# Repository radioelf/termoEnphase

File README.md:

# termoEnphase
Control de termo eléctrico según excedentes de sistema fotovoltaico con Enphase

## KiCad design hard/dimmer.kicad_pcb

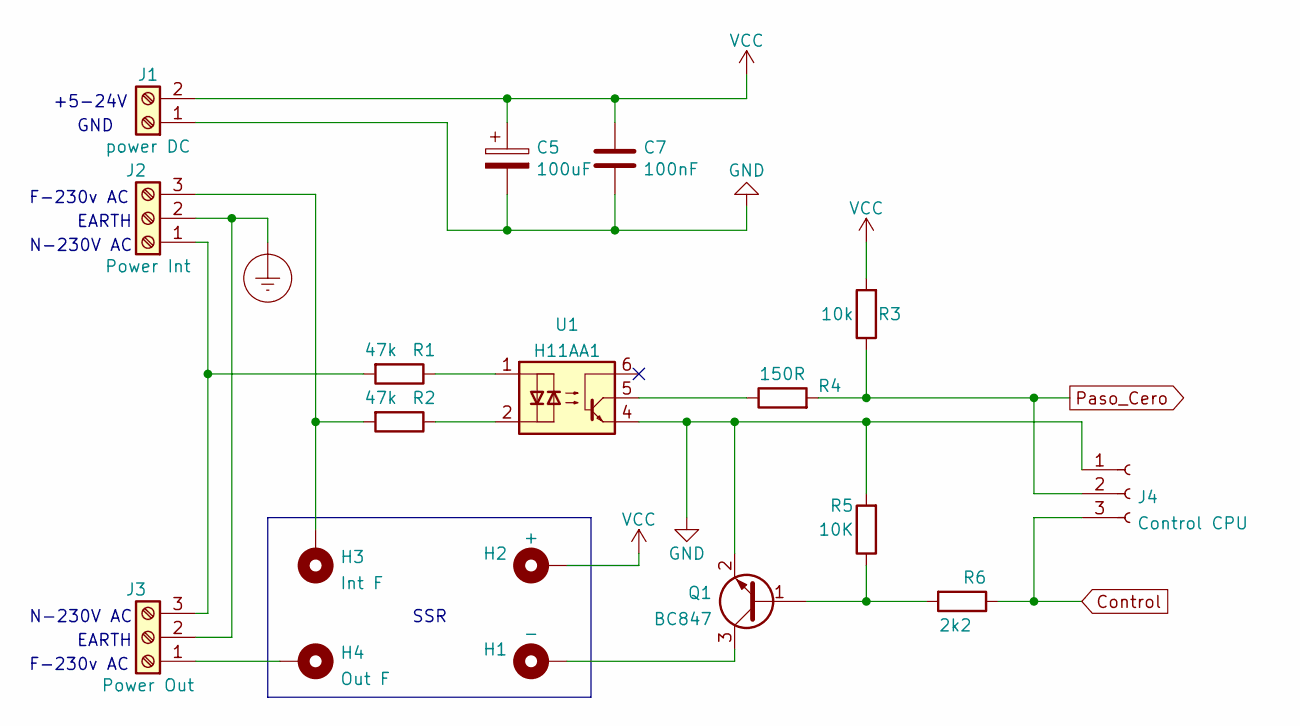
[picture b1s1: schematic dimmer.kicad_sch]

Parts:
C5: 100uF; CP_Elec_5x4.5
C7: 100nF; C_0805_2012Metric
H1: -; MountingHole_3.5mm_Pad_TopBottom
H2: +; MountingHole_3.5mm_Pad_TopBottom
H3: Int F; MountingHole_4.3mm_M4_DIN965_Pad_TopBottom
H4: Out F; MountingHole_4.3mm_M4_DIN965_Pad_TopBottom
J1: power DC; TerminalBlock_bornier-2_P5.08mm
J2: Power Int; TerminalBlock_bornier-3_P5.08mm
J3: Power Out; TerminalBlock_bornier-3_P5.08mm
J4: Control CPU; JST_EH_B3B-EH-A_1x03_P2.50mm_Vertical
Q1: BC847; SOT-23
R1, R2: 47k; R_Axial_DIN0411_L9.9mm_D3.6mm_P12.70mm_Horizontal
R3: 10k; R_0805_2012Metric
R4: 150R; R_0805_2012Metric
R5: 10K; R_0805_2012Metric
R6: 2k2; R_0805_2012Metric
U1: H11AA1; DIP-6_W7.62mm_SMDSocket_SmallPads

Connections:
Control: J4.3, R6.1
Earth_Protective: J2.2, J3.2
GND: C5.2, C7.2, J1.1, J4.1, Q1.2 (E), R5.2, U1.4
unnamed: H1.1, Q1.3 (C)
unnamed: H3.1, J2.3, R2.2
unnamed: H4.1, J3.1
unnamed: J2.1, J3.3, R1.2
unnamed: Q1.1 (B), R5.1, R6.2
unnamed: R1.1, U1.1
unnamed: R2.1, U1.2
unnamed: R4.1, U1.5
Paso_Cero: J4.2, R3.1, R4.2
VCC: C5.1, C7.1, H2.1, J1.2, R3.2

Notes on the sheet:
SSR
EARTH
N-230V AC
F-230v AC
+5-24V
GND

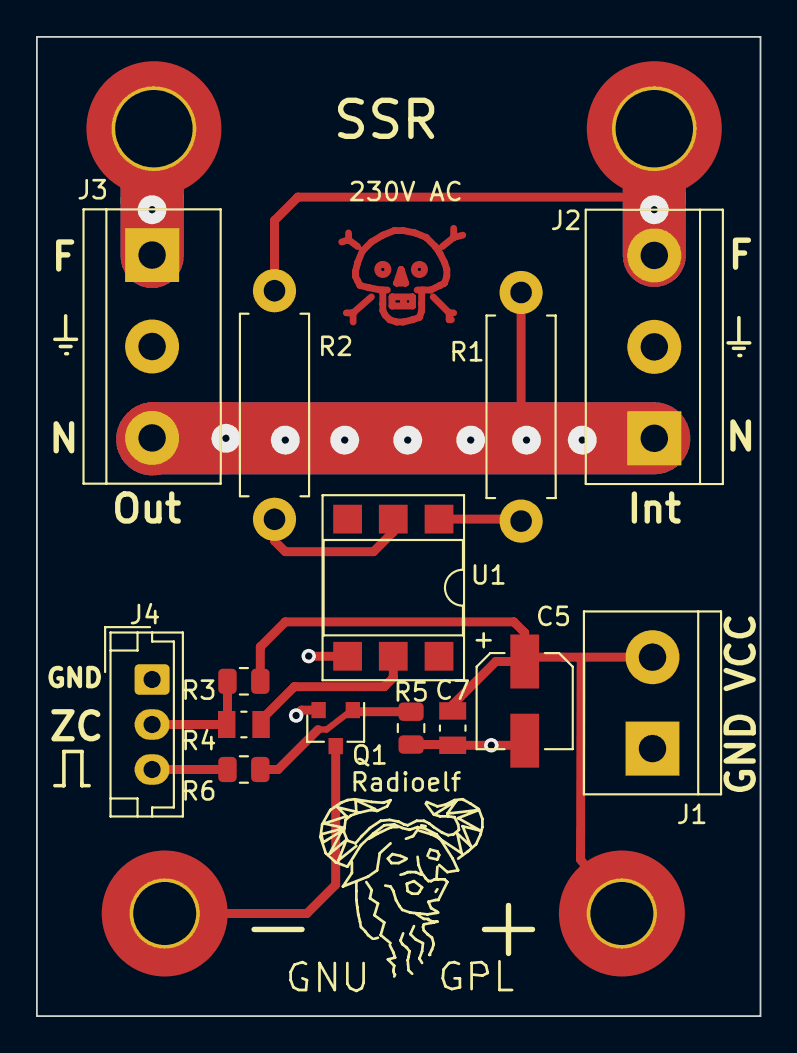
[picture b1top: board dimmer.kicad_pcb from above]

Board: 2 copper layers, 40.2 x 54.4 mm, 20 parts (0 on the bottom side), 13 nets.

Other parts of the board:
230V AC: Symbol_Danger_CopperTop_Small
Radioelf: Symbol_GNU-Logo_SilkscreenTop

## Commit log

2022-02-20 Create \hard
2022-02-20 Create \sof
2022-02-20 Update \hard
2022-02-20 Update \sof
